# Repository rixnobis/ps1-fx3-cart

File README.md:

# ps1-fx3-cart

A PlayStation expansion-port (PIO) cartridge built around a Cypress/Infineon FX3
(CYUSB3014) USB 3 controller. Every PIO signal the cart needs goes to the FX3's GPIF II
or GPIO pins, so the link protocol, DMA5, INT10, the I2S audio input and a CD-ROM
controller personality are firmware questions rather than board revisions. An optional
NOR flash behind the BIOS chip select (Switch Board) is programmed by code running on
the console.

Status: schematic in progress. Design notes and open questions: `docs/design.md`.

The board shares its FX3 core (power, clock, boot EEPROM, USB 3 routing) with
[ps1-av-capture](https://github.com/rixnobis/ps1-av-capture).

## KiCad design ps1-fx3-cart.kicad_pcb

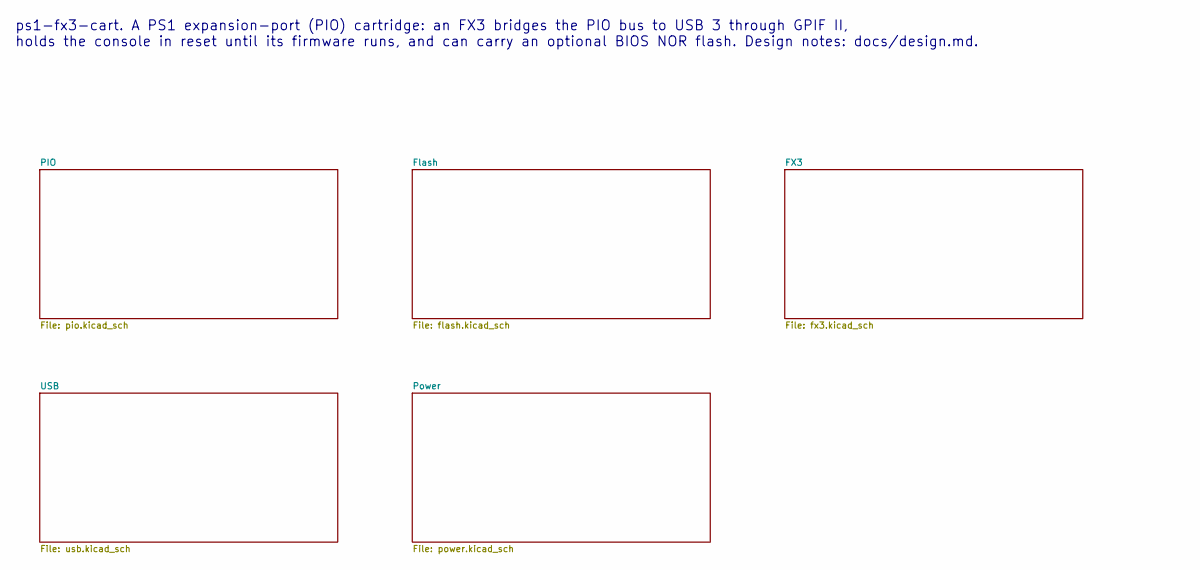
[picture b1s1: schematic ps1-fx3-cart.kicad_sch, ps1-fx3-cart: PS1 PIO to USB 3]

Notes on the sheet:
ps1-fx3-cart. A PS1 expansion-port (PIO) cartridge: an FX3 bridges the PIO bus to USB 3 through GPIF II, holds the console in reset until its firmware runs, and can carry an optional BIOS NOR flash. Design notes: docs/design.md.

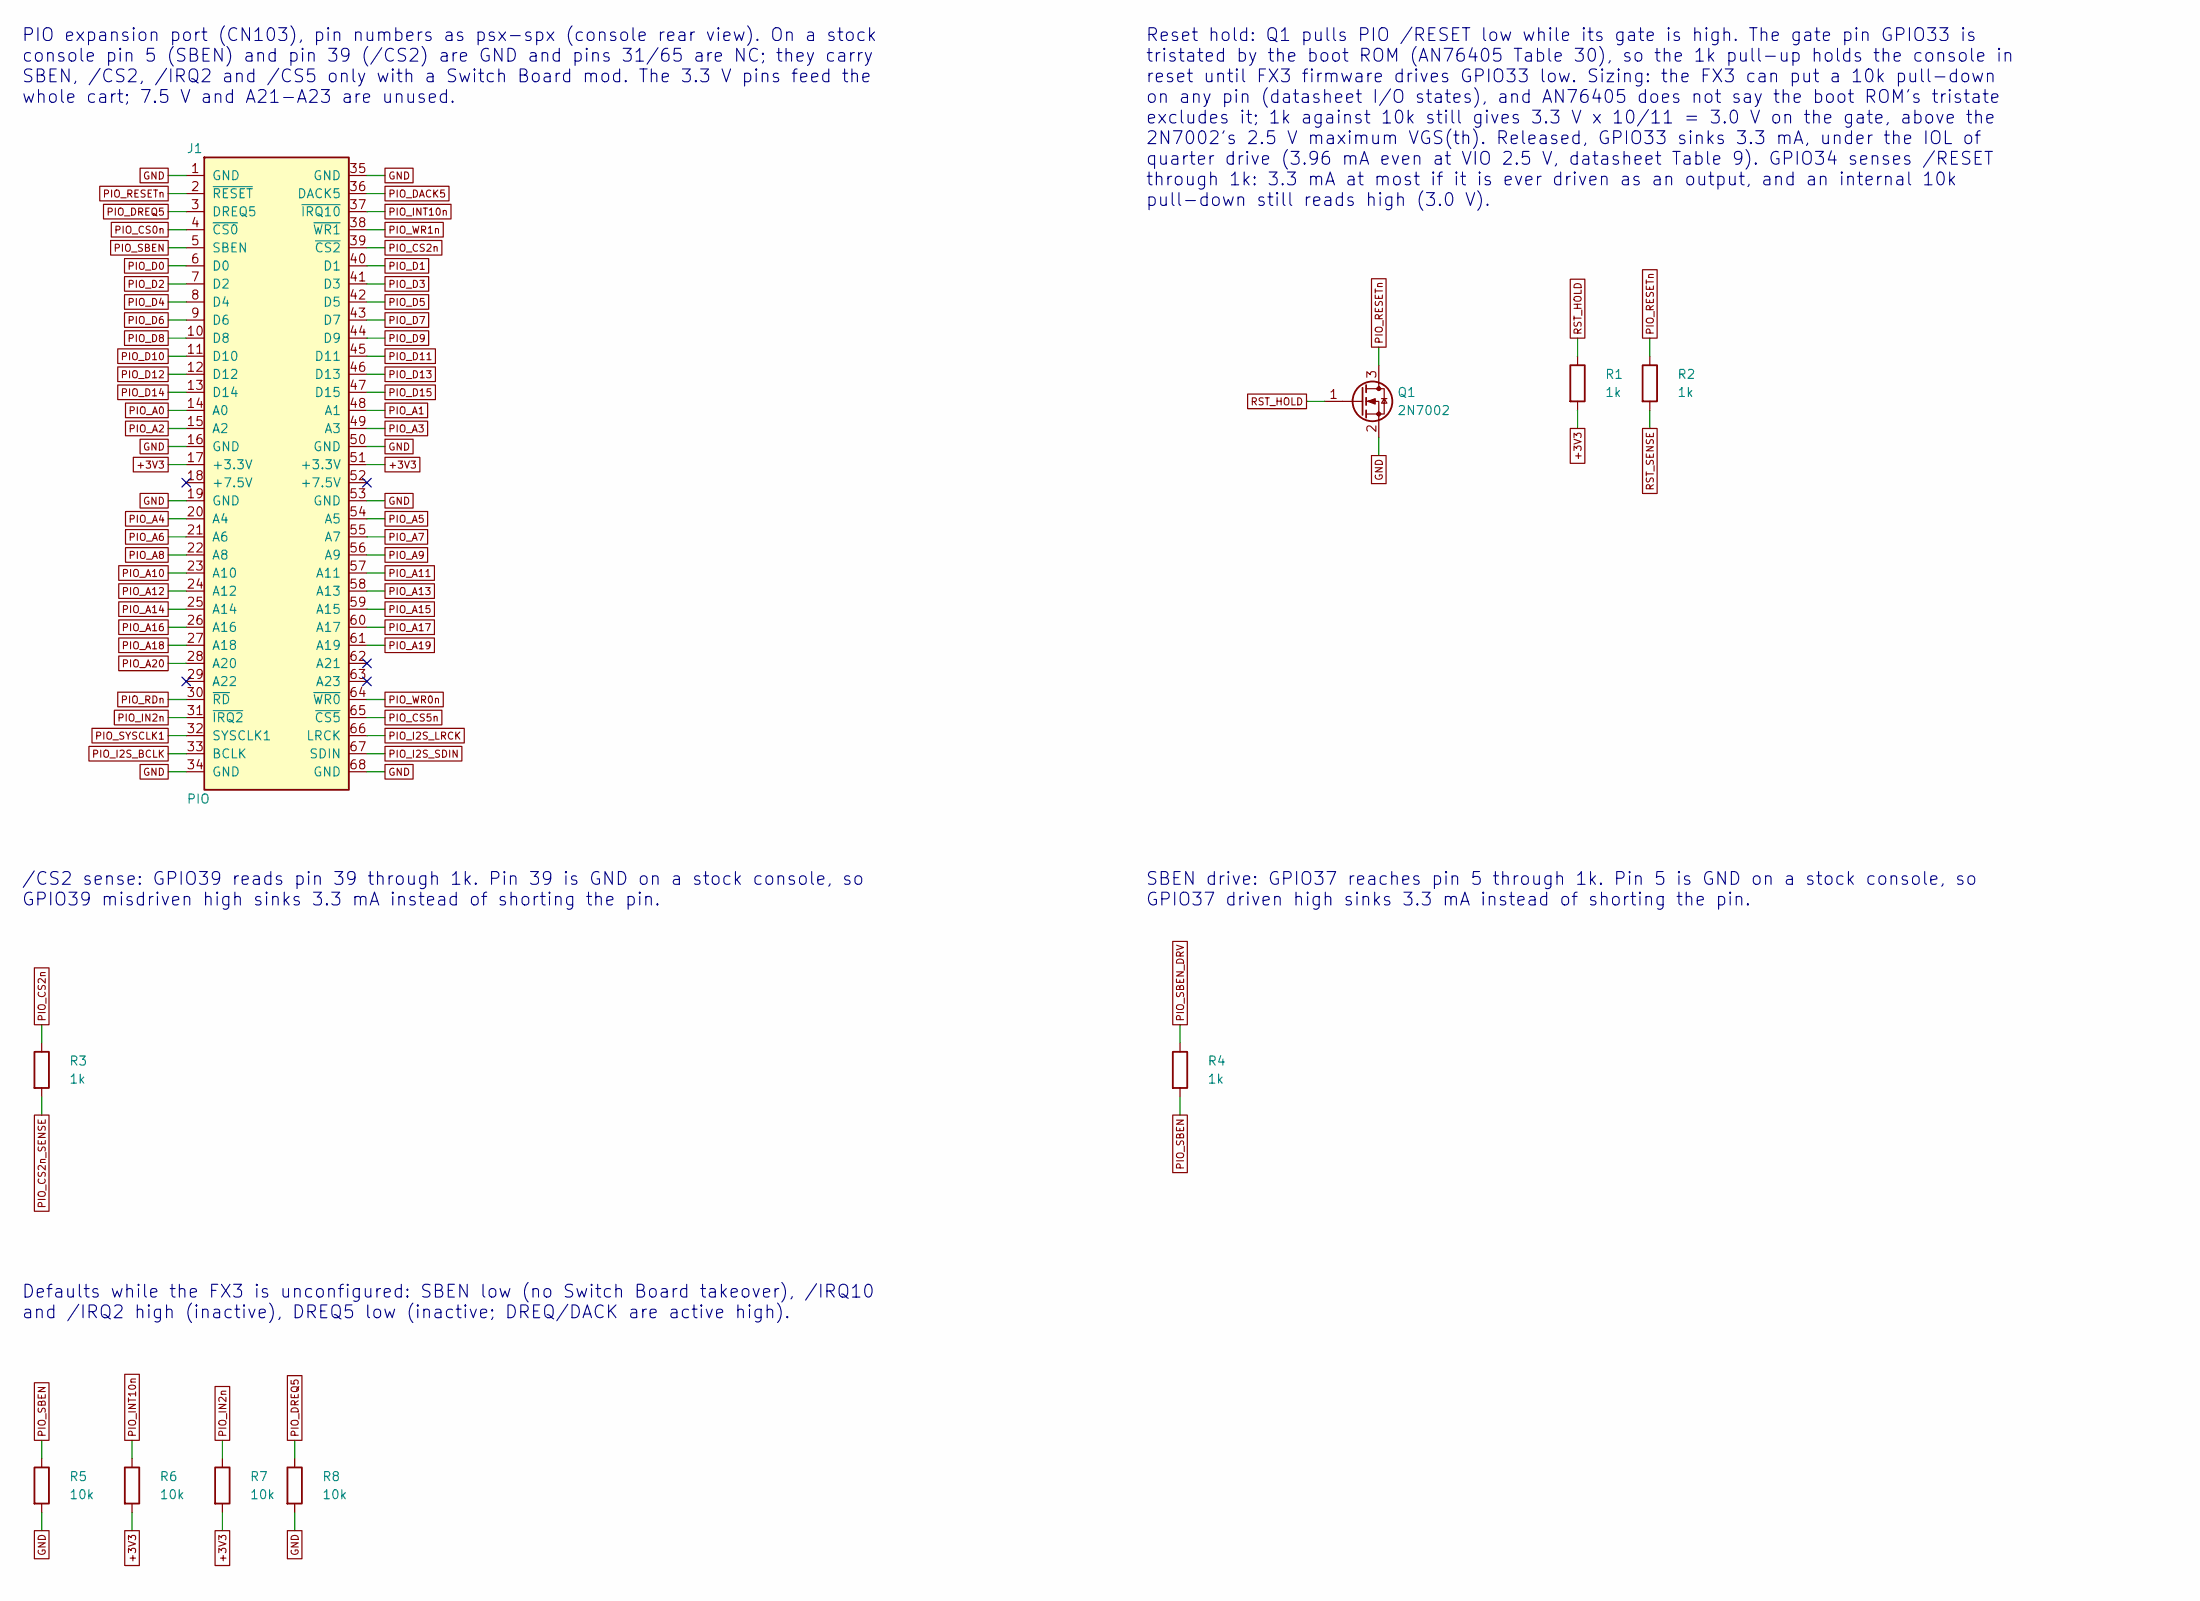
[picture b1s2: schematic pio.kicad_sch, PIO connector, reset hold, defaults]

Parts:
J1: PIO; PIOCONN
Q1: 2N7002; SOT-23; LCSC C8545
R1, R2, R3, R4: 1k; R_0402_1005Metric; LCSC C11702
R5, R6, R7, R8: 10k; R_0402_1005Metric; LCSC C25744

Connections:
+3V3: J1.17 (+3.3V), J1.51 (+3.3V), R1.2, R6.2, R7.2; also elsewhere on the board
GND: J1.1 (GND), J1.16 (GND), J1.19 (GND), J1.34 (GND), J1.35 (GND), J1.50 (GND), J1.53 (GND), J1.68 (GND), Q1.2 (S), R5.2, R8.2; also elsewhere on the board
PIO_A0: J1.14 (A0); also elsewhere on the board
PIO_A1: J1.48 (A1); also elsewhere on the board
PIO_A2: J1.15 (A2); also elsewhere on the board
PIO_A3: J1.49 (A3); also elsewhere on the board
PIO_A4: J1.20 (A4); also elsewhere on the board
PIO_A5: J1.54 (A5); also elsewhere on the board
PIO_A6: J1.21 (A6); also elsewhere on the board
PIO_A7: J1.55 (A7); also elsewhere on the board
PIO_A8: J1.22 (A8); also elsewhere on the board
PIO_A9: J1.56 (A9); also elsewhere on the board
PIO_A10: J1.23 (A10); also elsewhere on the board
PIO_A11: J1.57 (A11); also elsewhere on the board
PIO_A12: J1.24 (A12); also elsewhere on the board
PIO_A13: J1.58 (A13); also elsewhere on the board
PIO_A14: J1.25 (A14); also elsewhere on the board
PIO_A15: J1.59 (A15); also elsewhere on the board
PIO_A16: J1.26 (A16); also elsewhere on the board
PIO_A17: J1.60 (A17); also elsewhere on the board
PIO_A18: J1.27 (A18); also elsewhere on the board
PIO_A19: J1.61 (A19); also elsewhere on the board
PIO_A20: J1.28 (A20); also elsewhere on the board
PIO_CS0n: J1.4 (~CS0); also elsewhere on the board
PIO_CS2n: J1.39 (~CS2), R3.1; also elsewhere on the board
PIO_CS2n_SENSE: R3.2; also elsewhere on the board
PIO_CS5n: J1.65 (~CS5); also elsewhere on the board
PIO_D0: J1.6 (D0); also elsewhere on the board
PIO_D1: J1.40 (D1); also elsewhere on the board
PIO_D2: J1.7 (D2); also elsewhere on the board
PIO_D3: J1.41 (D3); also elsewhere on the board
PIO_D4: J1.8 (D4); also elsewhere on the board
PIO_D5: J1.42 (D5); also elsewhere on the board
PIO_D6: J1.9 (D6); also elsewhere on the board
PIO_D7: J1.43 (D7); also elsewhere on the board
PIO_D8: J1.10 (D8); also elsewhere on the board
PIO_D9: J1.44 (D9); also elsewhere on the board
PIO_D10: J1.11 (D10); also elsewhere on the board
PIO_D11: J1.45 (D11); also elsewhere on the board
PIO_D12: J1.12 (D12); also elsewhere on the board
PIO_D13: J1.46 (D13); also elsewhere on the board
PIO_D14: J1.13 (D14); also elsewhere on the board
PIO_D15: J1.47 (D15); also elsewhere on the board
PIO_DACK5: J1.36 (DACK5); also elsewhere on the board
PIO_DREQ5: J1.3 (DREQ5), R8.1; also elsewhere on the board
PIO_I2S_BCLK: J1.33 (BCLK); also elsewhere on the board
PIO_I2S_LRCK: J1.66 (LRCK); also elsewhere on the board
PIO_I2S_SDIN: J1.67 (SDIN); also elsewhere on the board
PIO_IN2n: J1.31 (~IRQ2), R7.1; also elsewhere on the board
PIO_INT10n: J1.37 (~IRQ10), R6.1; also elsewhere on the board
PIO_RDn: J1.30 (~RD); also elsewhere on the board
PIO_RESETn: J1.2 (~RESET), Q1.3 (D), R2.1; also elsewhere on the board
PIO_SBEN: J1.5 (SBEN), R4.2, R5.1
PIO_SBEN_DRV: R4.1; also elsewhere on the board
PIO_SYSCLK1: J1.32 (SYSCLK1); also elsewhere on the board
PIO_WR0n: J1.64 (~WR0); also elsewhere on the board
PIO_WR1n: J1.38 (~WR1); also elsewhere on the board
RST_HOLD: Q1.1 (G), R1.1; also elsewhere on the board
RST_SENSE: R2.2; also elsewhere on the board

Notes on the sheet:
PIO expansion port (CN103), pin numbers as psx-spx (console rear view). On a stock console pin 5 (SBEN) and pin 39 (/CS2) are GND and pins 31/65 are NC; they carry SBEN, /CS2, /IRQ2 and /CS5 only with a Switch Board mod. The 3.3 V pins feed the whole cart; 7.5 V and A21-A23 are unused.
Reset hold: Q1 pulls PIO /RESET low while its gate is high. The gate pin GPIO33 is tristated by the boot ROM (AN76405 Table 30), so the 1k pull-up holds the console in reset until FX3 firmware drives GPIO33 low. Sizing: the FX3 can put a 10k pull-down on any pin (datasheet I/O states), and AN76405 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
/CS2 sense: GPIO39 reads pin 39 through 1k. Pin 39 is GND on a stock console, so GPIO39 misdriven high sinks 3.3 mA instead of shorting the pin.
SBEN drive: GPIO37 reaches pin 5 through 1k. Pin 5 is GND on a stock console, so GPIO37 driven high sinks 3.3 mA instead of shorting the pin.
Defaults while the FX3 is unconfigured: SBEN low (no Switch Board takeover), /IRQ10 and /IRQ2 high (inactive), DREQ5 low (inactive; DREQ/DACK are active high).

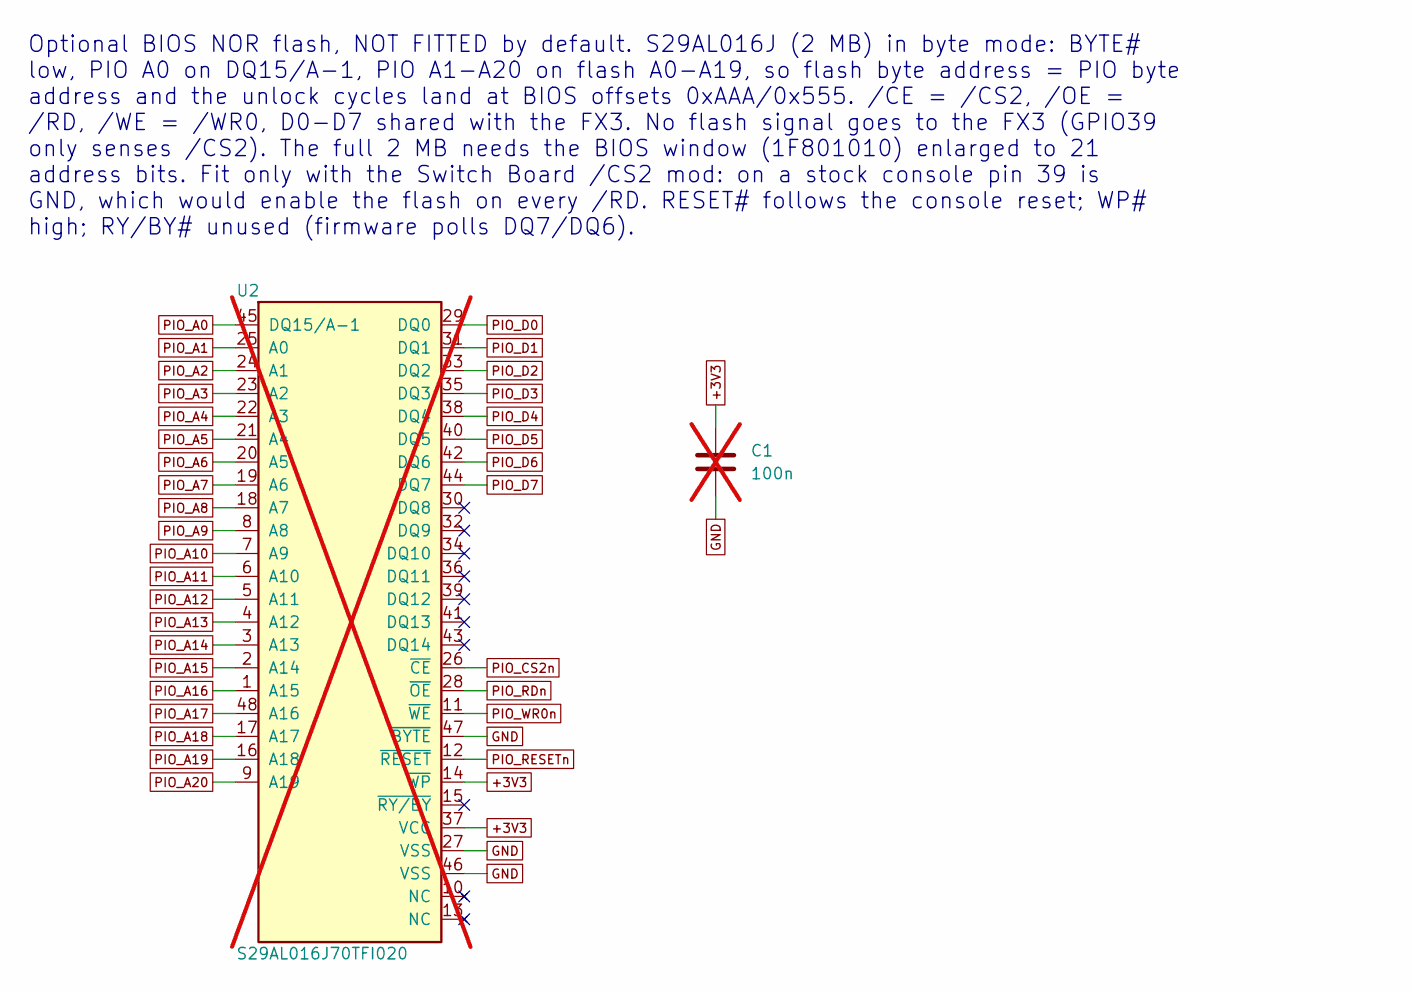
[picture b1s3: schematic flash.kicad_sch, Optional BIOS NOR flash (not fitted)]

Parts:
C1: 100n; C_0402_1005Metric; LCSC C1525; not fitted
U2: S29AL016J70TFI020; TSOP-I-48_18.4x12mm_P0.5mm; LCSC C914935; not fitted

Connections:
+3V3: C1.1, U2.14 (~WP), U2.37 (VCC); also elsewhere on the board
GND: C1.2, U2.27 (VSS), U2.46 (VSS), U2.47 (~BYTE); also elsewhere on the board
PIO_A0: U2.45 (DQ15/A-1); also elsewhere on the board
PIO_A1: U2.25 (A0); also elsewhere on the board
PIO_A2: U2.24 (A1); also elsewhere on the board
PIO_A3: U2.23 (A2); also elsewhere on the board
PIO_A4: U2.22 (A3); also elsewhere on the board
PIO_A5: U2.21 (A4); also elsewhere on the board
PIO_A6: U2.20 (A5); also elsewhere on the board
PIO_A7: U2.19 (A6); also elsewhere on the board
PIO_A8: U2.18 (A7); also elsewhere on the board
PIO_A9: U2.8 (A8); also elsewhere on the board
PIO_A10: U2.7 (A9); also elsewhere on the board
PIO_A11: U2.6 (A10); also elsewhere on the board
PIO_A12: U2.5 (A11); also elsewhere on the board
PIO_A13: U2.4 (A12); also elsewhere on the board
PIO_A14: U2.3 (A13); also elsewhere on the board
PIO_A15: U2.2 (A14); also elsewhere on the board
PIO_A16: U2.1 (A15); also elsewhere on the board
PIO_A17: U2.48 (A16); also elsewhere on the board
PIO_A18: U2.17 (A17); also elsewhere on the board
PIO_A19: U2.16 (A18); also elsewhere on the board
PIO_A20: U2.9 (A19); also elsewhere on the board
PIO_CS2n: U2.26 (~CE); also elsewhere on the board
PIO_D0: U2.29 (DQ0); also elsewhere on the board
PIO_D1: U2.31 (DQ1); also elsewhere on the board
PIO_D2: U2.33 (DQ2); also elsewhere on the board
PIO_D3: U2.35 (DQ3); also elsewhere on the board
PIO_D4: U2.38 (DQ4); also elsewhere on the board
PIO_D5: U2.40 (DQ5); also elsewhere on the board
PIO_D6: U2.42 (DQ6); also elsewhere on the board
PIO_D7: U2.44 (DQ7); also elsewhere on the board
PIO_RDn: U2.28 (~OE); also elsewhere on the board
PIO_RESETn: U2.12 (~RESET); also elsewhere on the board
PIO_WR0n: U2.11 (~WE); also elsewhere on the board

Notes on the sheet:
Optional BIOS NOR flash, NOT FITTED by default. S29AL016J (2 MB) in byte mode: BYTE# low, PIO A0 on DQ15/A-1, PIO A1-A20 on flash A0-A19, so flash byte address = PIO byte address and the unlock cycles land at BIOS offsets 0xAAA/0x555. /CE = /CS2, /OE = /RD, /WE = /WR0, D0-D7 shared with the FX3. No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
